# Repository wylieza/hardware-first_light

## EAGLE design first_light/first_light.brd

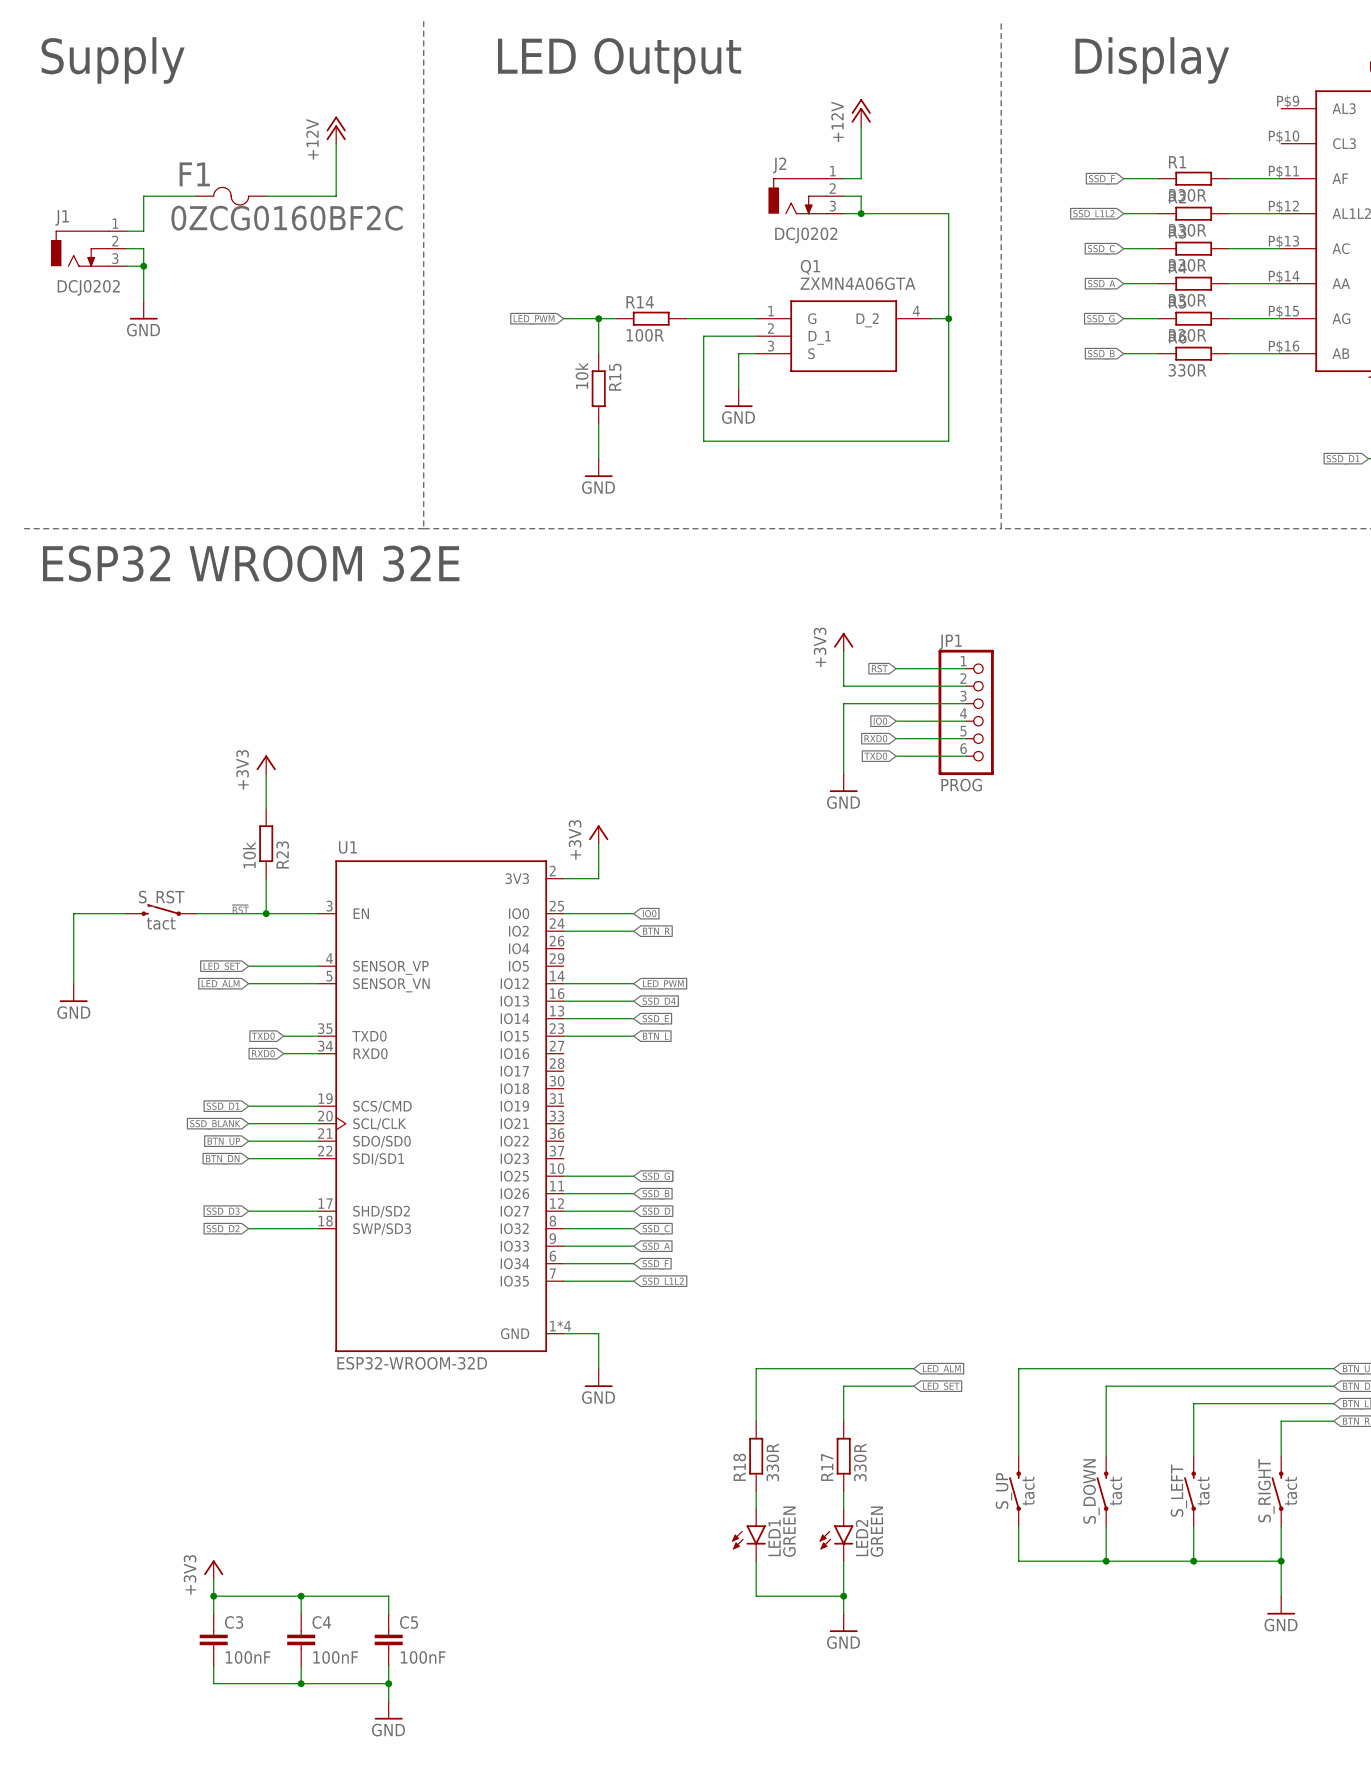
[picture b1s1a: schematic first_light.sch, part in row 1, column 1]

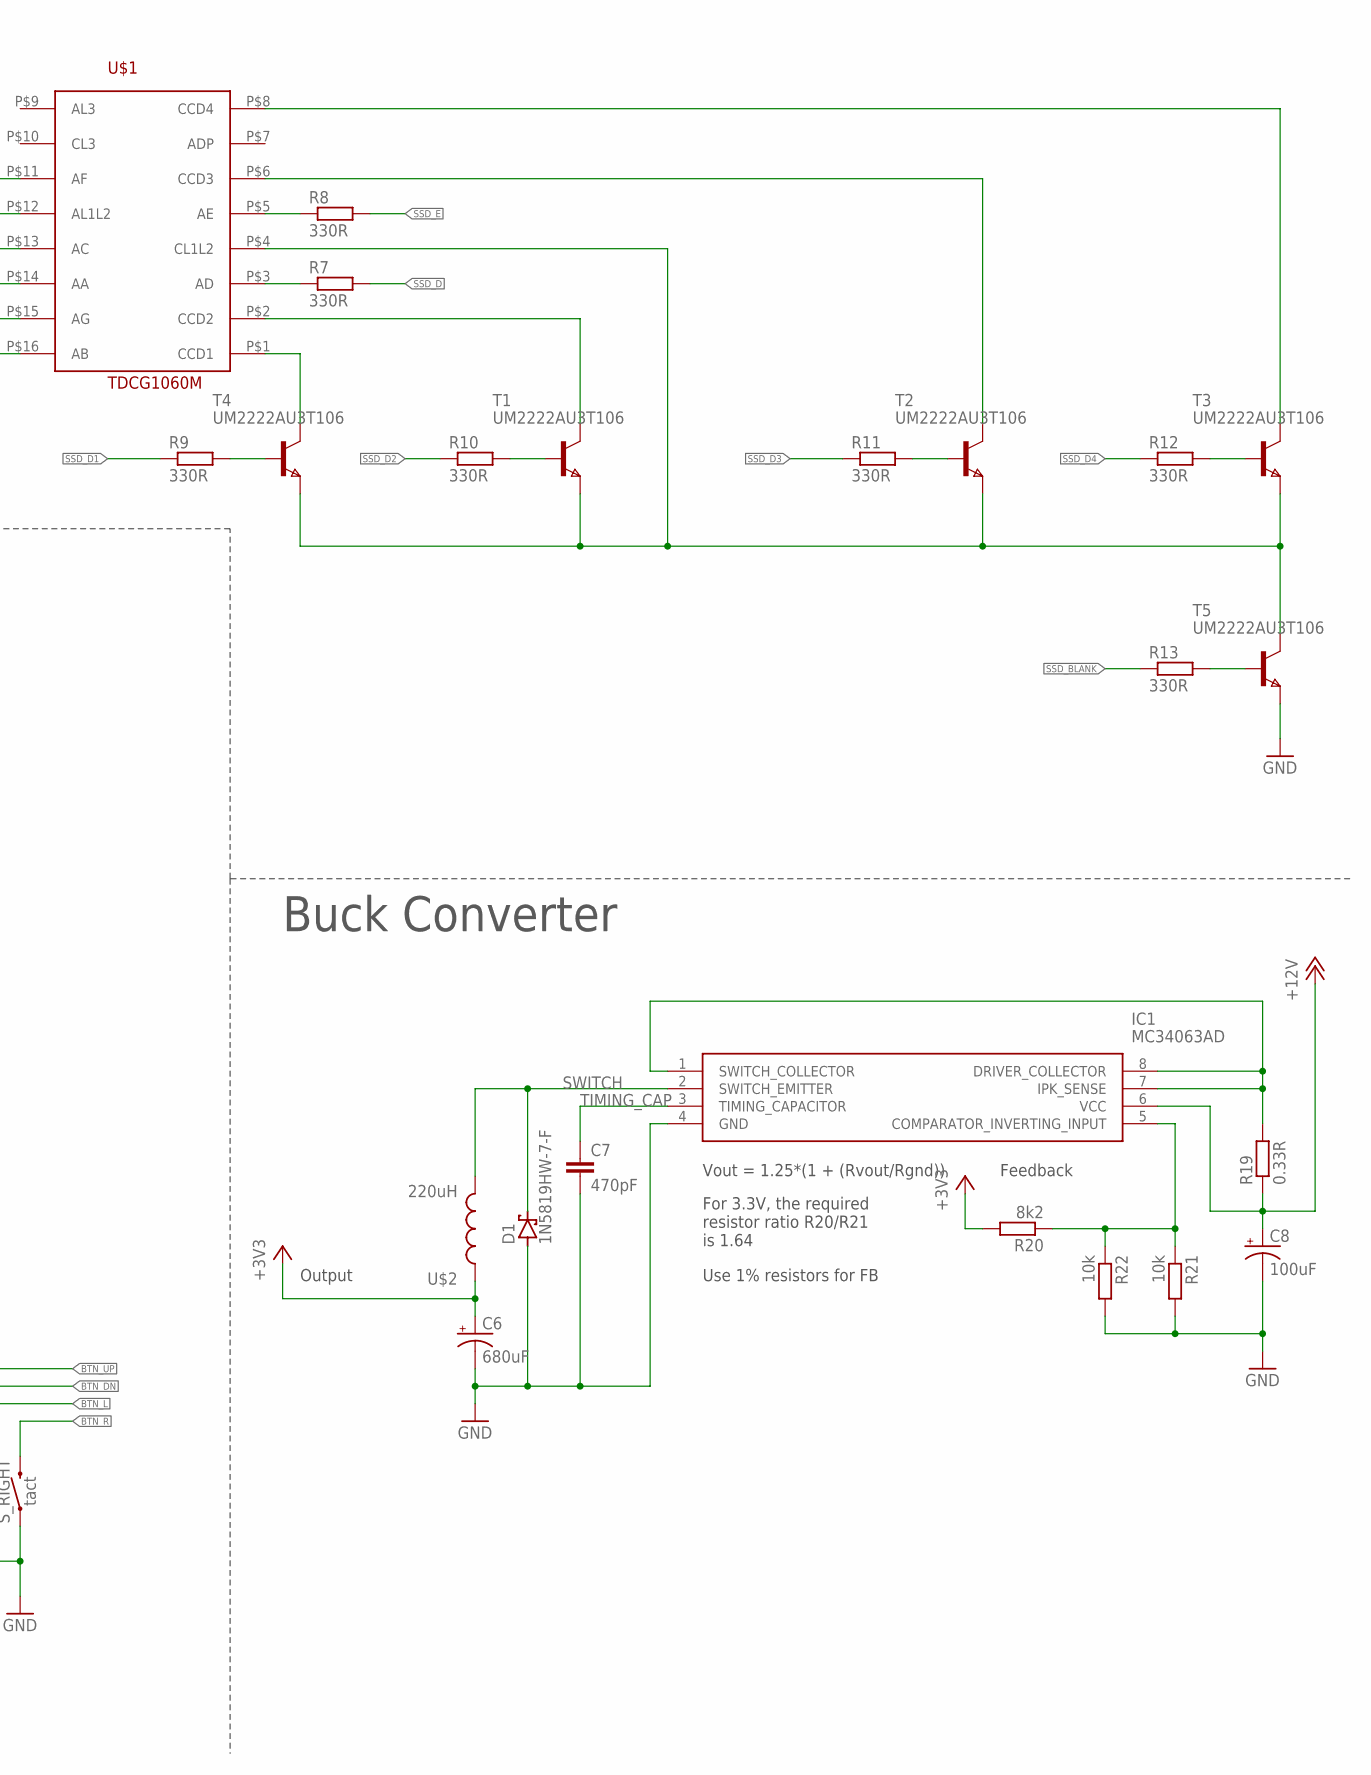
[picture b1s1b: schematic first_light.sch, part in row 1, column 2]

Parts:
C3, C4, C5: 100nF; C0603
C6: 680uF; 153CLV-0605
C7: 470pF; C0603
C8: 100uF; 153CLV-0605
D1: SCHOTTKY-1N5819HW-7-F; SOD123
F1: 0ZCG0160BF2C; 0ZCG_BEL
IC1: MC34063AD; SOIC127P600X175-8N
J1, J2: DCJ0202
JP1: PROG; 1X06
LED1, LED2: GREEN; CHIP-LED0603
Q1: ZXMN4A06GTA; SOT230P700X180-4N
R1, R2, R3, R4, R5, R6, R7, R8, R9, R10, R11, R12, R13, R17, R18: 330R; R0603
R14: 100R; R0603
R15, R21, R22, R23: 10k; R0603
R19: 0.33R; R0603
R20: 8k2; R0603
S_DOWN: tact; TACTILE_SWITCH_PTH_6.0MM
S_LEFT: tact; TACTILE_SWITCH_PTH_6.0MM
S_RIGHT: tact; TACTILE_SWITCH_PTH_6.0MM
S_RST: tact; TACTILE_SWITCH_PTH_6.0MM
S_UP: tact; TACTILE_SWITCH_PTH_6.0MM
T1, T2, T3, T4, T5: UM2222AU3T106; SOT323
U1: ESP32-WROOM-32D; MODULE_ESP32-WROOM-32D
U$1: TDCG1060M
U$2: 220uH; 1010_INDUCTOR

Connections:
!RST: JP1.1, R23.1, S_RST.1, U1.3 (EN)
+3V3: C3.1, C4.1, C5.1, C6.+, JP1.2, R20.2, R23.2, U1.2 (3V3), U$2.1
+12V: C8.+, F1.2, IC1.6 (VCC), J2.1, R19.1
BTN_DN: S_DOWN.3 (2), U1.22 (SDI/SD1)
BTN_L: S_LEFT.3 (2), U1.23 (IO15)
BTN_R: S_RIGHT.3 (2), U1.24 (IO2)
BTN_UP: S_UP.3 (2), U1.21 (SDO/SD0)
GND: C3.2, C4.2, C5.2, C6.-, C7.2, C8.-, D1.2 (A), IC1.4 (GND), J1.2, J1.3, JP1.3, LED1.C, LED2.C, Q1.3 (S), R15.2, R21.2, R22.2, S_DOWN.1, S_LEFT.1, S_RIGHT.1, S_RST.3 (2), S_UP.1, T5.3 (E), U1.1 (GND), U1.15 (GND), U1.38 (GND), U1.39 (GND)
IO0: JP1.4, U1.25 (IO0)
LED_ALM: R18.2, U1.5 (SENSOR_VN)
LED_PWM: R14.1, R15.1, U1.14 (IO12)
LED_SET: R17.2, U1.4 (SENSOR_VP)
unnamed: R1.2, U$1.P$11 (AF)
unnamed: R2.2, U$1.P$12 (AL1L2)
unnamed: R3.2, U$1.P$13 (AC)
unnamed: R4.2, U$1.P$14 (AA)
unnamed: R5.2, U$1.P$15 (AG)
unnamed: R6.2, U$1.P$16 (AB)
unnamed: R7.1, U$1.P$3 (AD)
unnamed: R8.1, U$1.P$5 (AE)
unnamed: T4.1 (C), U$1.P$1 (CCD1)
unnamed: T1.1 (C), U$1.P$2 (CCD2)
unnamed: T2.1 (C), U$1.P$6 (CCD3)
unnamed: T3.1 (C), U$1.P$8 (CCD4)
unnamed: T1.3 (E), T2.3 (E), T3.3 (E), T4.3 (E), T5.1 (C), U$1.P$4 (CL1L2)
unnamed: R13.2, T5.2 (B)
unnamed: R12.2, T3.2 (B)
unnamed: R11.2, T2.2 (B)
unnamed: R10.2, T1.2 (B)
unnamed: R9.2, T4.2 (B)
unnamed: J2.2, J2.3, Q1.2 (D_1), Q1.4 (D_2)
unnamed: Q1.1 (G), R14.2
unnamed: LED2.A, R17.1
unnamed: LED1.A, R18.1
unnamed: IC1.1 (SWITCH_COLLECTOR), IC1.7 (IPK_SENSE), IC1.8 (DRIVER_COLLECTOR), R19.2
unnamed: IC1.5 (COMPARATOR_INVERTING_INPUT), R20.1, R21.1, R22.1
unnamed: F1.1, J1.1
RXD0: JP1.5, U1.34 (RXD0)
SSD_A: R4.1, U1.9 (IO33)
SSD_B: R6.1, U1.11 (IO26)
SSD_BLANK: R13.1, U1.20 (SCL/CLK)
SSD_C: R3.1, U1.8 (IO32)
SSD_D: R7.2, U1.12 (IO27)
SSD_D1: R9.1, U1.19 (SCS/CMD)
SSD_D2: R10.1, U1.18 (SWP/SD3)
SSD_D3: R11.1, U1.17 (SHD/SD2)
SSD_D4: R12.1, U1.16 (IO13)
SSD_E: R8.2, U1.13 (IO14)
SSD_F: R1.1, U1.6 (IO34)
SSD_G: R5.1, U1.10 (IO25)
SSD_L1L2: R2.1, U1.7 (IO35)
SWITCH: D1.1 (C), IC1.2 (SWITCH_EMITTER), U$2.2
TIMING_CAP: C7.1, IC1.3 (TIMING_CAPACITOR)
TXD0: JP1.6, U1.35 (TXD0)

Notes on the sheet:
Supply
LED Output
Display
ESP32 WROOM 32E
Buck Converter
Feedback
Output
Vout = 1.25*(1 + (Rvout/Rgnd))
For 3.3V, the required resistor ratio R20/R21 is 1.64
Use 1% resistors for FB

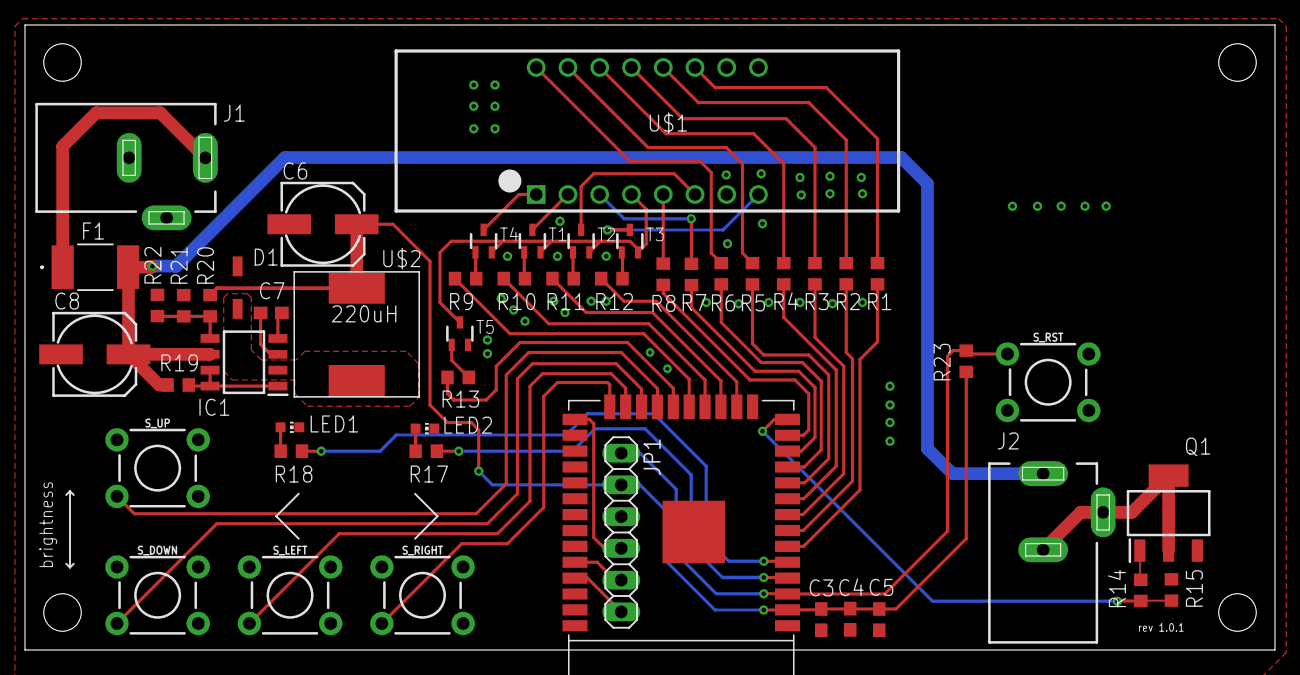
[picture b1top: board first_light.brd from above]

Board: 2 copper layers, 100.0 x 50.0 mm, 50 parts (0 on the bottom side), 54 nets.

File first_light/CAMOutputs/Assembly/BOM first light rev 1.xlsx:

Qty | Value | Device | Package | Parts | Description | ARROW_PART_NUMBER | ARROW_PRICE-STOCK | AVAILABILITY | COPYRIGHT | DESCRIPTION | DKPN | HEIGHT | MANUFACTURER_NAME | MANUFACTURER_PART_NUMBER | MF | MFPN | MFR_NAME | MOUSER_PART_NUMBER | MOUSER_PRICE-STOCK | MP | MPN | OC_FARNELL | OC_NEWARK | PACKAGE | POPULARITY | PRICE | PROD_ID | SF_SKU | SPICEPREFIX
1.0 | 0.33R | R-EU_R0603 | R0603 | R19 | RESISTOR, European symbol |  |  |  |  |  | P17485CT-ND |  |  |  |  | ERJ-3BWJR033V |  |  |  |  |  |  |  |  | 70.0 |  |  |  | R
1.0 | 0ZCG0160BF2C | 0ZCG0160BF2C | 0ZCG_BEL | F1 |  |  |  |  | Copyright (C) 2021 Ultra Librarian. All rights reserved. |  | 507-1776-1-ND |  |  | 0ZCG0160BF2C |  | 0ZCG0160BF2C | Belfuse
1.0 | 100R | R-EU_R0603 | R0603 | R14 | RESISTOR, European symbol |  |  |  |  |  | 311-100GRCT-ND |  |  |  |  | RC0603JR-07100RL |  |  |  |  |  |  |  |  | 70.0 |  |  |  | R
3.0 | 100nF | C-EUC0603 | C0603 | C3, C4, C5 | CAPACITOR, European symbol |  |  |  |  |  | 1276-1935-1-ND |  |  |  |  | CL10B104KB8NNWC |  |  |  |  |  |  |  |  |  |  |  |  | C
1.0 | 100uF | CPOL-US153CLV-0605 | 153CLV-0605 | C8 | POLARIZED CAPACITOR, American symbol |  |  |  |  |  | 2616-VE-101M1CTR-0605S-ND |  |  |  |  | VE-101M1CTR-0605S |  |  |  |  |  |  |  |  | 8.0 |  |  |  | C
4.0 | 10k | R-EU_R0603 | R0603 | R15, R21, R22, R23 | RESISTOR, European symbol |  |  |  |  |  | 13-RC0603JR-1010KLCT-ND |  |  |  |  | RC0603JR-1010KL |  |  |  |  |  |  |  |  | 70.0 |  |  |  | R
1.0 | 220uH | 1010_INDUCTOR | 1010_INDUCTOR | U$2 |  |  |  |  |  |  | 732-4110-1-ND |  |  |  |  | 7.447714221E9
15.0 | 330R | R-EU_R0603 | R0603 | R1, R2, R3, R4, R5, R6, R7, R8, R9, R10, R11, R12, R13, R17, R18 | RESISTOR, European symbol |  |  |  |  |  | 311-330GRCT-ND |  |  |  |  | RC0603JR-07330RL |  |  |  |  |  |  |  |  | 70.0 |  |  |  | R
1.0 | 470pF | C-EUC0603 | C0603 | C7 | CAPACITOR, European symbol |  |  |  |  |  | 1276-1094-1-ND |  |  |  |  | CL10B471KB8NNNC |  |  |  |  |  |  |  |  | 73.0 |  |  |  | C
1.0 | 680uF | CPOL-US153CLV-0605 | 153CLV-0605 | C6 | POLARIZED CAPACITOR, American symbol |  |  |  |  |  | 565-5128-1-ND |  |  |  |  | EMZR6R3ARA681MF80G |  |  |  |  |  |  |  |  | 8.0 |  |  |  | C
1.0 | 8k2 | R-EU_R0603 | R0603 | R20 | RESISTOR, European symbol |  |  |  |  |  | 311-8.2KGRCT-ND |  |  |  |  | RC0603JR-078K2L |  |  |  |  |  |  |  |  | 70.0 |  |  |  | R
2.0 | DCJ0202 | DCJ0202 | DCJ0202 | J1, J2 | DC POWER JACK |  |  |  |  |  | 2092-KLDX-0202-BC-ND |  |  |  |  | KLDX-0202-BC |  |  |  |  |  | unknown | unknown |  | 17.0
1.0 | ESP32-WROOM-32D | ESP32-WROOM-32D | MODULE_ESP32-WROOM-32D | U1 | IC: SoC; GPIO, I2C, I2S, IR, SD, SDIO, SPI, UART; 2.7÷3.6VDC; 20dBm |  |  | Unavailable |  | IC: SoC | GPIO, I2C, I2S, IR, SD, SDIO, SPI, UART | 2.7÷3.6VDC | 20dBm | 1965-ESP32-WROOM-32E-H4CT-ND |  |  |  | Espressif Systems | ESP32-WROOM-32E-H4 |  |  |  | ESP32-WROOM-32D |  |  |  | Module Espressif Systems |  | None
2.0 | GREEN | LEDCHIP-LED0603 | CHIP-LED0603 | LED1, LED2 | LED |  |  |  |  |  | 732-4980-1-ND |  |  |  |  | 150060VS75000 |  |  |  |  |  |  |  |  | 26.0
1.0 | MC34063AD | MC34063AD | SOIC127P600X175-8N | IC1 | Step up/down converter,MC34063AD 98pcs | MC34063AD | https://www.arrow.com/en/products/mc34063ad/on-semiconductor |  |  | Step up/down converter,MC34063AD 98pcs | MC34063ADR2GOSCT-ND | 1.75mm | ON Semiconductor | MC34063AD |  | MC34063ADR2G |  | 512-MC34063AD | http://www.mouser.com/Search/ProductDetail.aspx?qs=qJQOsIEC8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
1.0 | PROG | PINHD-1X6 | 1X06 | JP1 | PIN HEADER |  |  |  |  |  |  |  |  |  |  |  |  |  |  |  |  |  |  |  | 79.0
1.0 | SCHOTTKY-1N5819HW-7-F | SCHOTTKY-1N5819HW-7-F | SOD123 | D1 |  |  |  |  |  |  | 1N5819HW-FDICT-ND |  |  |  |  | 1N5819HW-7-F
1.0 | TDCG1060M | TDCG1060M | TDCG1060M | U$1 |  |  |  |  |  |  | TDCG1060M-ND |  |  |  |  | TDCG1060M
5.0 | UM2222AU3T106 | NPNSOT323 | SOT323 | T1, T2, T3, T4, T5 | NPN TRANSISTOR |  |  |  |  |  | 846-UM2222AU3T106CT-ND |  |  |  |  | UM2222AU3T106 |  |  |  |  | DSS4160U-7 | 1710696.0 | 25R4558 |  | 2.0
1.0 | ZXMN4A06GTA | ZXMN4A06GTA | SOT230P700X180-4N | Q1 | MOSFET 40V N-Chnl UMOS | ZXMN4A06GTA | https://www.arrow.com/en/products/zxmn4a06gta/diodes-incorpo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 |  |  | MOSFET 40V N-Chnl UMOS | ZXMN4A06GCT-ND | 1.8mm | Diodes Inc. | ZXMN4A06GTA |  | ZXMN4A06GTA |  | 522-ZXMN4A06GTA | https://www.mouser.co.uk/ProductDetail/Diodes-Incorporated/Z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
5.0 | tact | MOMENTARY-SWITCH-SPST-PTH-6.0MM | TACTILE_SWITCH_PTH_6.0MM | S_DOWN, S_LEFT, S_RIGHT, S_RST, S_UP | Momentary Switch (Pushbutton) - SPST |  |  |  |  |  | 2223-TS02-66-60-BK-100-LCR-D-ND |  |  |  |  | TS02-66-60-BK-100-LCR-D |  |  |  |  |  |  |  |  |  |  | SWCH-08441 | COM-00097

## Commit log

2021-09-24 created eagle project
2021-09-24 basic layout
2021-10-01 progress on schematic design
2021-10-03 added buck regulator and fused input
2021-10-04 created a board and grouped parts by function
2022-01-20 more layout work
2022-01-29 layout work
2022-01-30 now using esp32 due to no stm available
2022-02-20 wired up ssd to esp
2022-02-26 last adjustments before new layout
2022-02-26 working on new layout
2022-05-08 layout and routing
2022-05-14 finished layout and routing
2022-05-15 board designator positioning
2022-05-16 finishing touches and export gerbers
2022-05-17 added vias for a better ground plane and too fill between some tracks"
2022-05-21 added MFPN and DKPN for all parts + exported BOM
2022-07-09 added dimension for 3d enclosure design

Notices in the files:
parts and their libraries:
SparkFun-Switches: Licensing: Creative Commons ShareAlike 4.0 International - https://creativecommons.org/licenses/by-sa/4.0
COPYRIGHT: Copyright (C) 2021 Ultra Librarian. All rights reserved.
